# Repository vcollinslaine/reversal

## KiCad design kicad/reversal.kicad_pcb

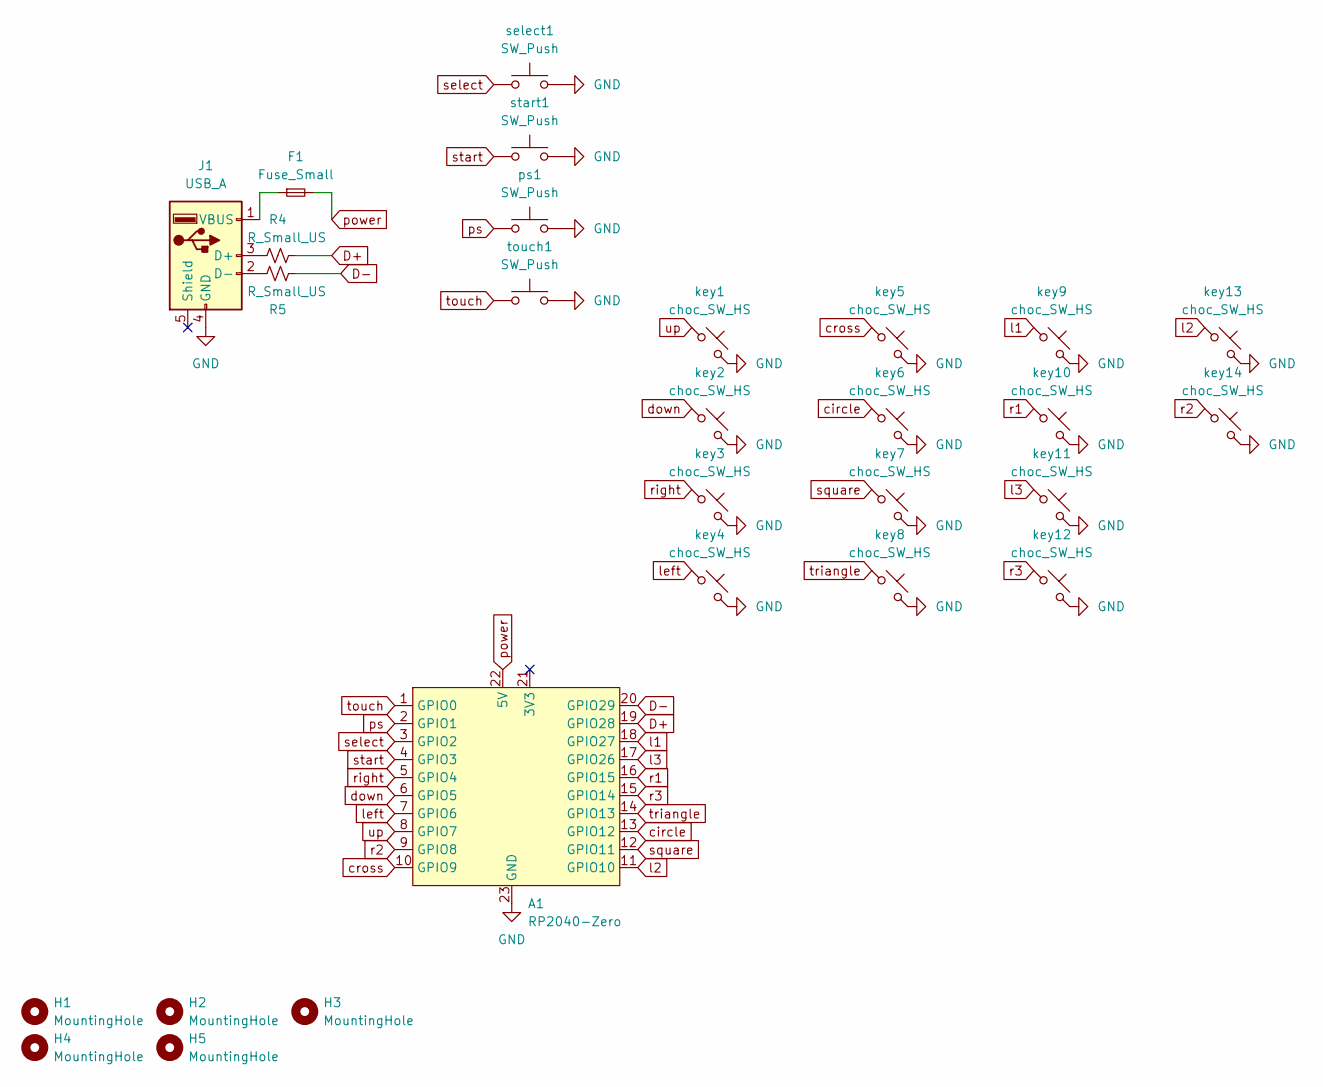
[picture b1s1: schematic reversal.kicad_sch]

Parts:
A1: RP2040-Zero
F1: Fuse_Small; Fuse_1206_3216Metric_Pad1.42x1.75mm_HandSolder
H1, H2, H3, H4, H5: MountingHole; MountingHole_6.4mm_M6
J1: USB_A; USB_A_Female_C42425
R4, R5: R_Small_US; R_0402_1005Metric_Pad0.72x0.64mm_HandSolder
key1, key2, key3, key4, key5, key6, key7, key8, key9, key10, key11, key12, key13, key14: choc_SW_HS; Kailh_socket_PG1350_optional
ps1: SW_Push; SW_PUSH_6mm
select1: SW_Push; SW_PUSH_6mm
start1: SW_Push; SW_PUSH_6mm
touch1: SW_Push; SW_PUSH_6mm

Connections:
D+: A1.19 (GPIO28), R4.1
D-: A1.20 (GPIO29), R5.2
GND: A1.23 (GND), J1.4 (GND), key1.2, key2.2, key3.2, key4.2, key5.2, key6.2, key7.2, key8.2, key9.2, key10.2, key11.2, key12.2, key13.2, key14.2, ps1.2, select1.2, start1.2, touch1.2
unnamed: J1.3 (D+), R4.2
unnamed: J1.2 (D-), R5.1
unnamed: F1.1, J1.1 (VBUS)
circle: A1.13 (GPIO12), key6.1
cross: A1.10 (GPIO9), key5.1
down: A1.6 (GPIO5), key2.1
l1: A1.18 (GPIO27), key9.1
l2: A1.11 (GPIO10), key13.1
l3: A1.17 (GPIO26), key11.1
left: A1.7 (GPIO6), key4.1
power: A1.22 (5V), F1.2
ps: A1.2 (GPIO1), ps1.1
r1: A1.16 (GPIO15), key10.1
r2: A1.9 (GPIO8), key14.1
r3: A1.15 (GPIO14), key12.1
right: A1.5 (GPIO4), key3.1
select: A1.3 (GPIO2), select1.1
square: A1.12 (GPIO11), key7.1
start: A1.4 (GPIO3), start1.1
touch: A1.1 (GPIO0), touch1.1
triangle: A1.14 (GPIO13), key8.1
up: A1.8 (GPIO7), key1.1

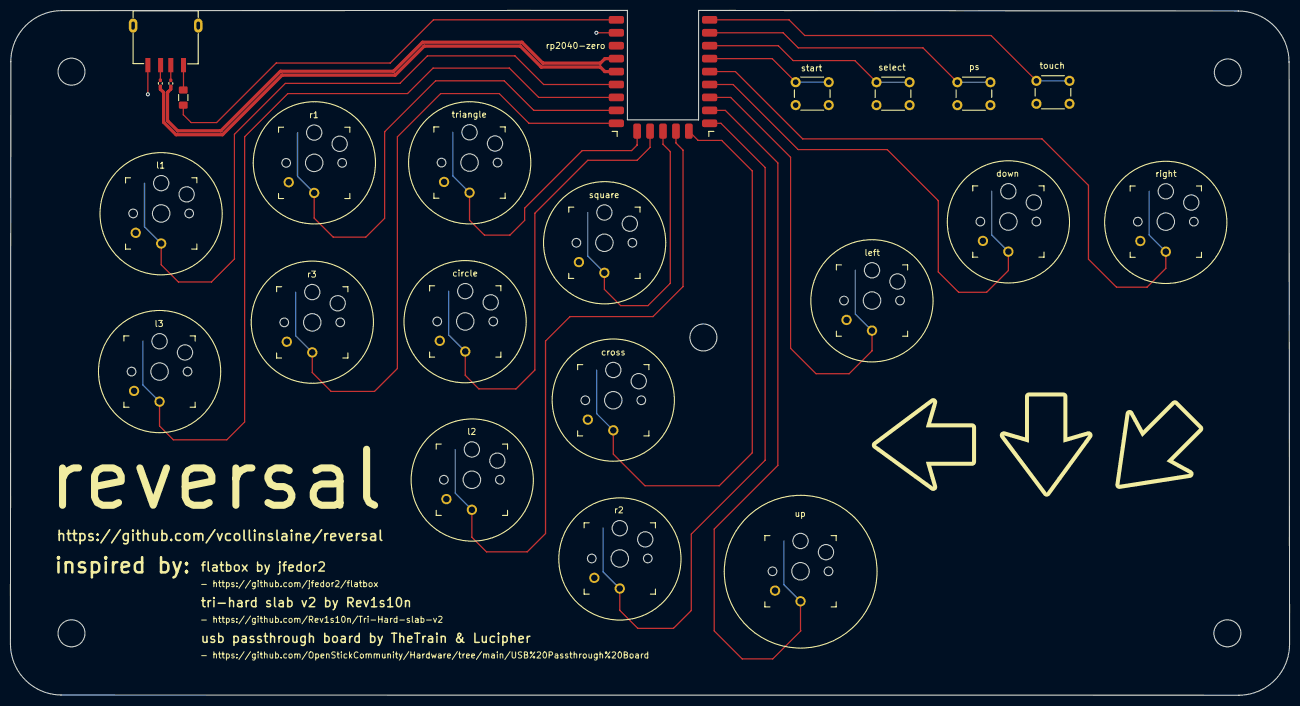
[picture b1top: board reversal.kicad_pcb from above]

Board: 2 copper layers, 251.2 x 134.5 mm, 28 parts (0 on the bottom side), 25 nets.

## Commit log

2024-02-04 Uploaded kicad v1 for reversal PCB
2024-02-04 reduced left edge of pcb
2024-02-04 Added touch button & rerouted traces to accomodate
2024-02-04 Fixed library linking issues
2024-02-04 trace beautification
2024-02-06 Matched differential pair to usb2 spec
